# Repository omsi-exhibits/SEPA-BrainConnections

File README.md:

# OMSI's Brain Connections

## Next Steps
* update accelerometer code to use timers instead of delays
* update all the code to use timers instead of delays

## Other Todos
* consolodate notes
* write a good readme
* document High Level Design

## Known Bugs
none atm

# Flashing new firmware
The Itsybitsy32u4_5v is a litte finiky when it comes to flashing. The process that works most of the time for me is to double press the reset button
and then super quickly upload the code. Like within 300milliseconds or less. Maybe disabling serial.print()s would help? 

# Troubleshooting Tips
Removing and reinserting microcontroller is delicate and needs you to support the bottom of the mainboard with your hand.

## Fun Ideas
* Easter Egg Color pallette swap
* Sensor held on startup could change colors
* Handheld brain-connections game-thing

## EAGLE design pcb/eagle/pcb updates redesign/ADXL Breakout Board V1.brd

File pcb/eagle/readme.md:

sorry the file names are a mess. these were made before git versioning.
Use the highest numbered file names. If that is not it then its the newest written files.

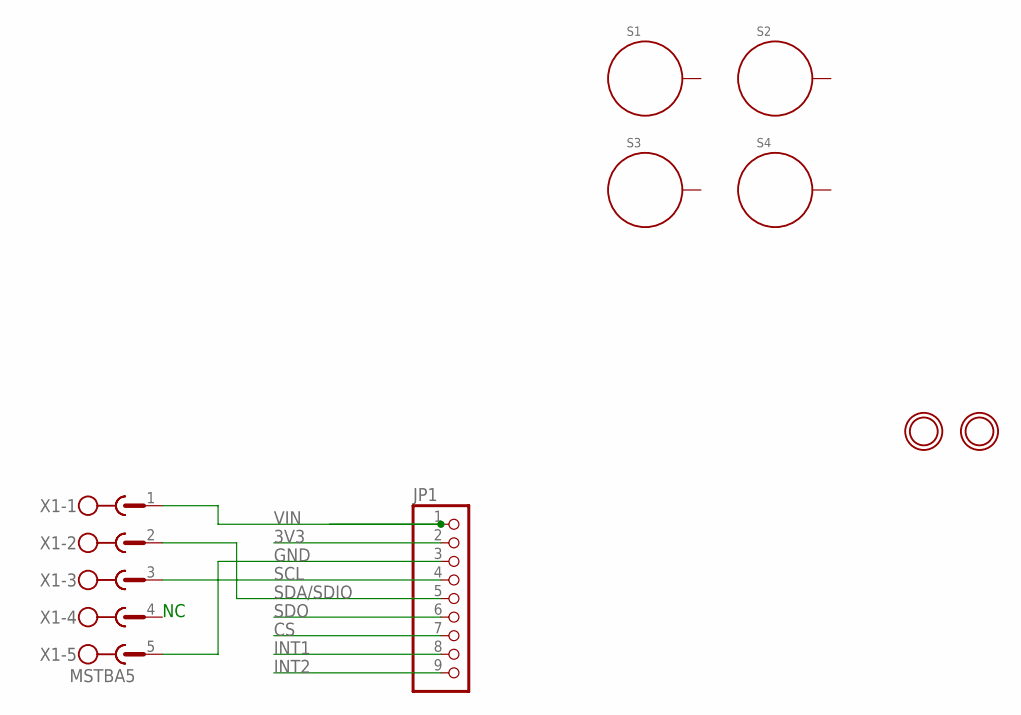
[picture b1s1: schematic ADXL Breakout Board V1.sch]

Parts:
JP1: HEADER-1X970MIL; 1X09_ROUND_70
S1, S2, S3, S4: STANDOFF_ELECTRICAL5-32; STANDOFF_ELECTRICAL_5_32
U$4, U$6: MOUNTINGHOLE2.5; MOUNTINGHOLE_2.5_PLATED
X1: MSTBA5

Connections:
3V3: JP1.2
CS: JP1.7
GND: JP1.3, X1.5
INT1: JP1.8
INT2: JP1.9
SCL: JP1.4, X1.3
SDA/SDIO: JP1.5, X1.2
SDO: JP1.6
VIN: JP1.1, X1.1

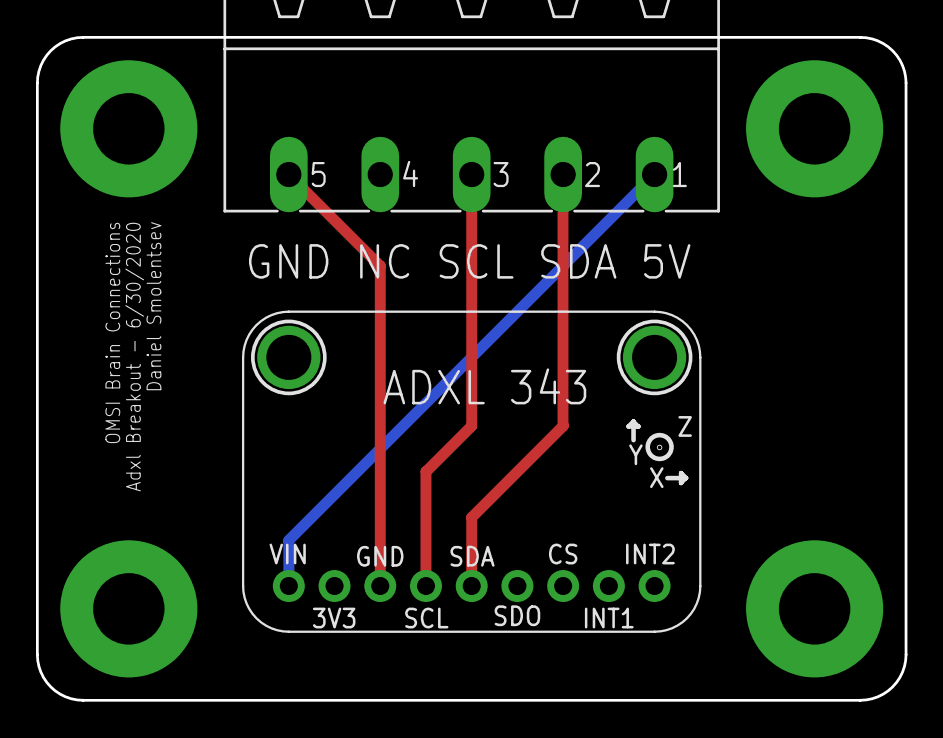
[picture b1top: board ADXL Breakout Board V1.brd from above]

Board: 2 copper layers, 48.3 x 36.8 mm, 8 parts (0 on the bottom side), 4 nets.

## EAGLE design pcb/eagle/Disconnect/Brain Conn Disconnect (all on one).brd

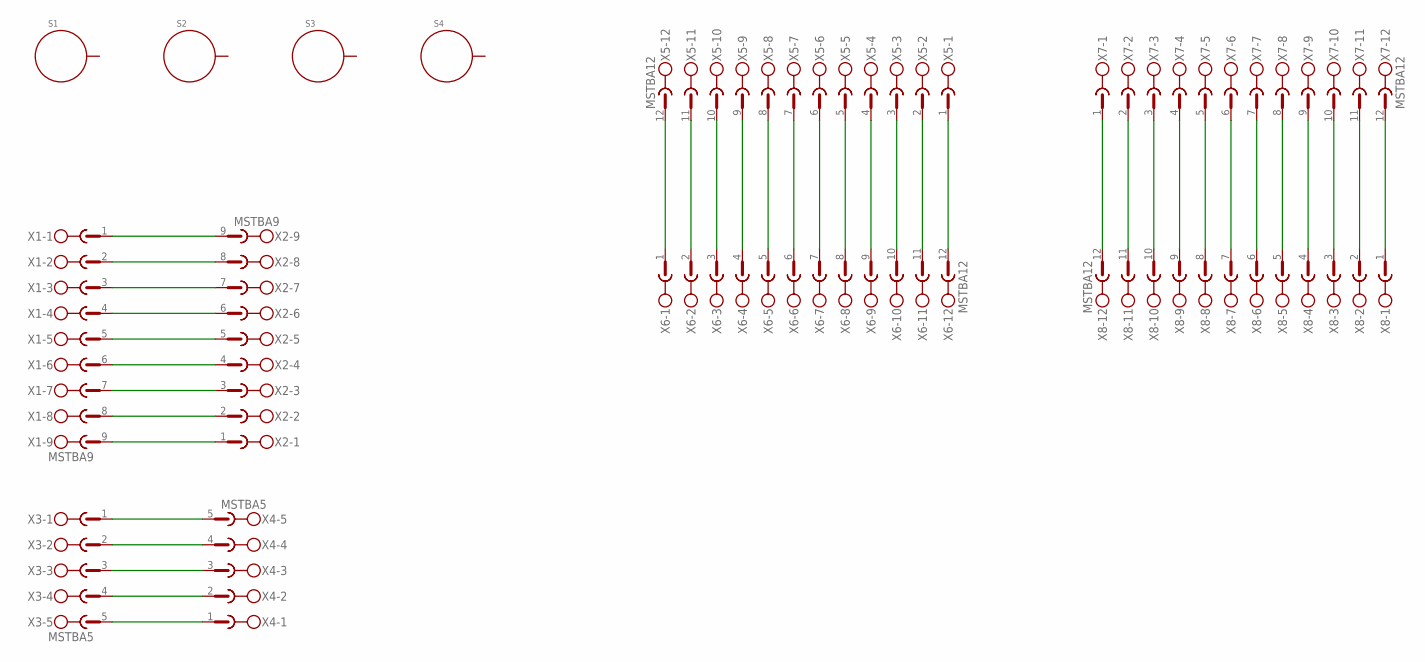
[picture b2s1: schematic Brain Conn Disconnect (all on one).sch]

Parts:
S1, S2, S3, S4: STANDOFF_ELECTRICAL144; STANDOFF_ELECTRICAL_144MILL_NORMAL_SCREW
X1, X2: MSTBA9
X3, X4: MSTBA5
X5, X6, X7, X8: MSTBA12

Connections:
unnamed: X3.1, X4.5
unnamed: X3.2, X4.4
unnamed: X3.3, X4.3
unnamed: X3.4, X4.2
unnamed: X3.5, X4.1
unnamed: X1.1, X2.9
unnamed: X1.2, X2.8
unnamed: X1.3, X2.7
unnamed: X1.4, X2.6
unnamed: X1.5, X2.5
unnamed: X1.6, X2.4
unnamed: X1.7, X2.3
unnamed: X1.8, X2.2
unnamed: X1.9, X2.1
unnamed: X5.12, X6.1
unnamed: X5.11, X6.2
unnamed: X5.10, X6.3
unnamed: X5.9, X6.4
unnamed: X5.8, X6.5
unnamed: X5.7, X6.6
unnamed: X5.6, X6.7
unnamed: X5.5, X6.8
unnamed: X5.4, X6.9
unnamed: X5.3, X6.10
unnamed: X5.2, X6.11
unnamed: X5.1, X6.12
unnamed: X7.1, X8.12
unnamed: X7.2, X8.11
unnamed: X7.3, X8.10
unnamed: X7.4, X8.9
unnamed: X7.5, X8.8
unnamed: X7.6, X8.7
unnamed: X7.7, X8.6
unnamed: X7.8, X8.5
unnamed: X7.9, X8.4
unnamed: X7.10, X8.3
unnamed: X7.11, X8.2
unnamed: X7.12, X8.1

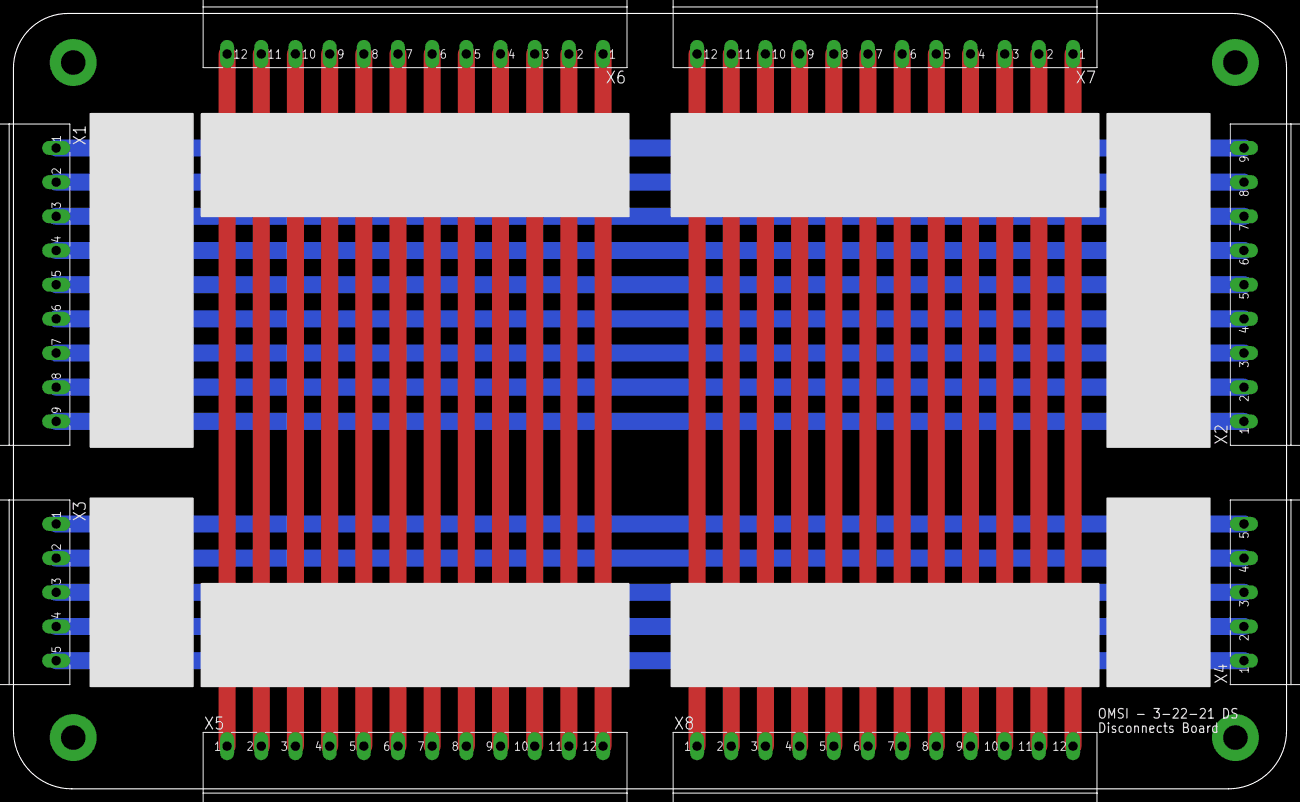
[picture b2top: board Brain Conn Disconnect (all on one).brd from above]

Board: 2 copper layers, 189.2 x 115.2 mm, 12 parts (0 on the bottom side), 38 nets.

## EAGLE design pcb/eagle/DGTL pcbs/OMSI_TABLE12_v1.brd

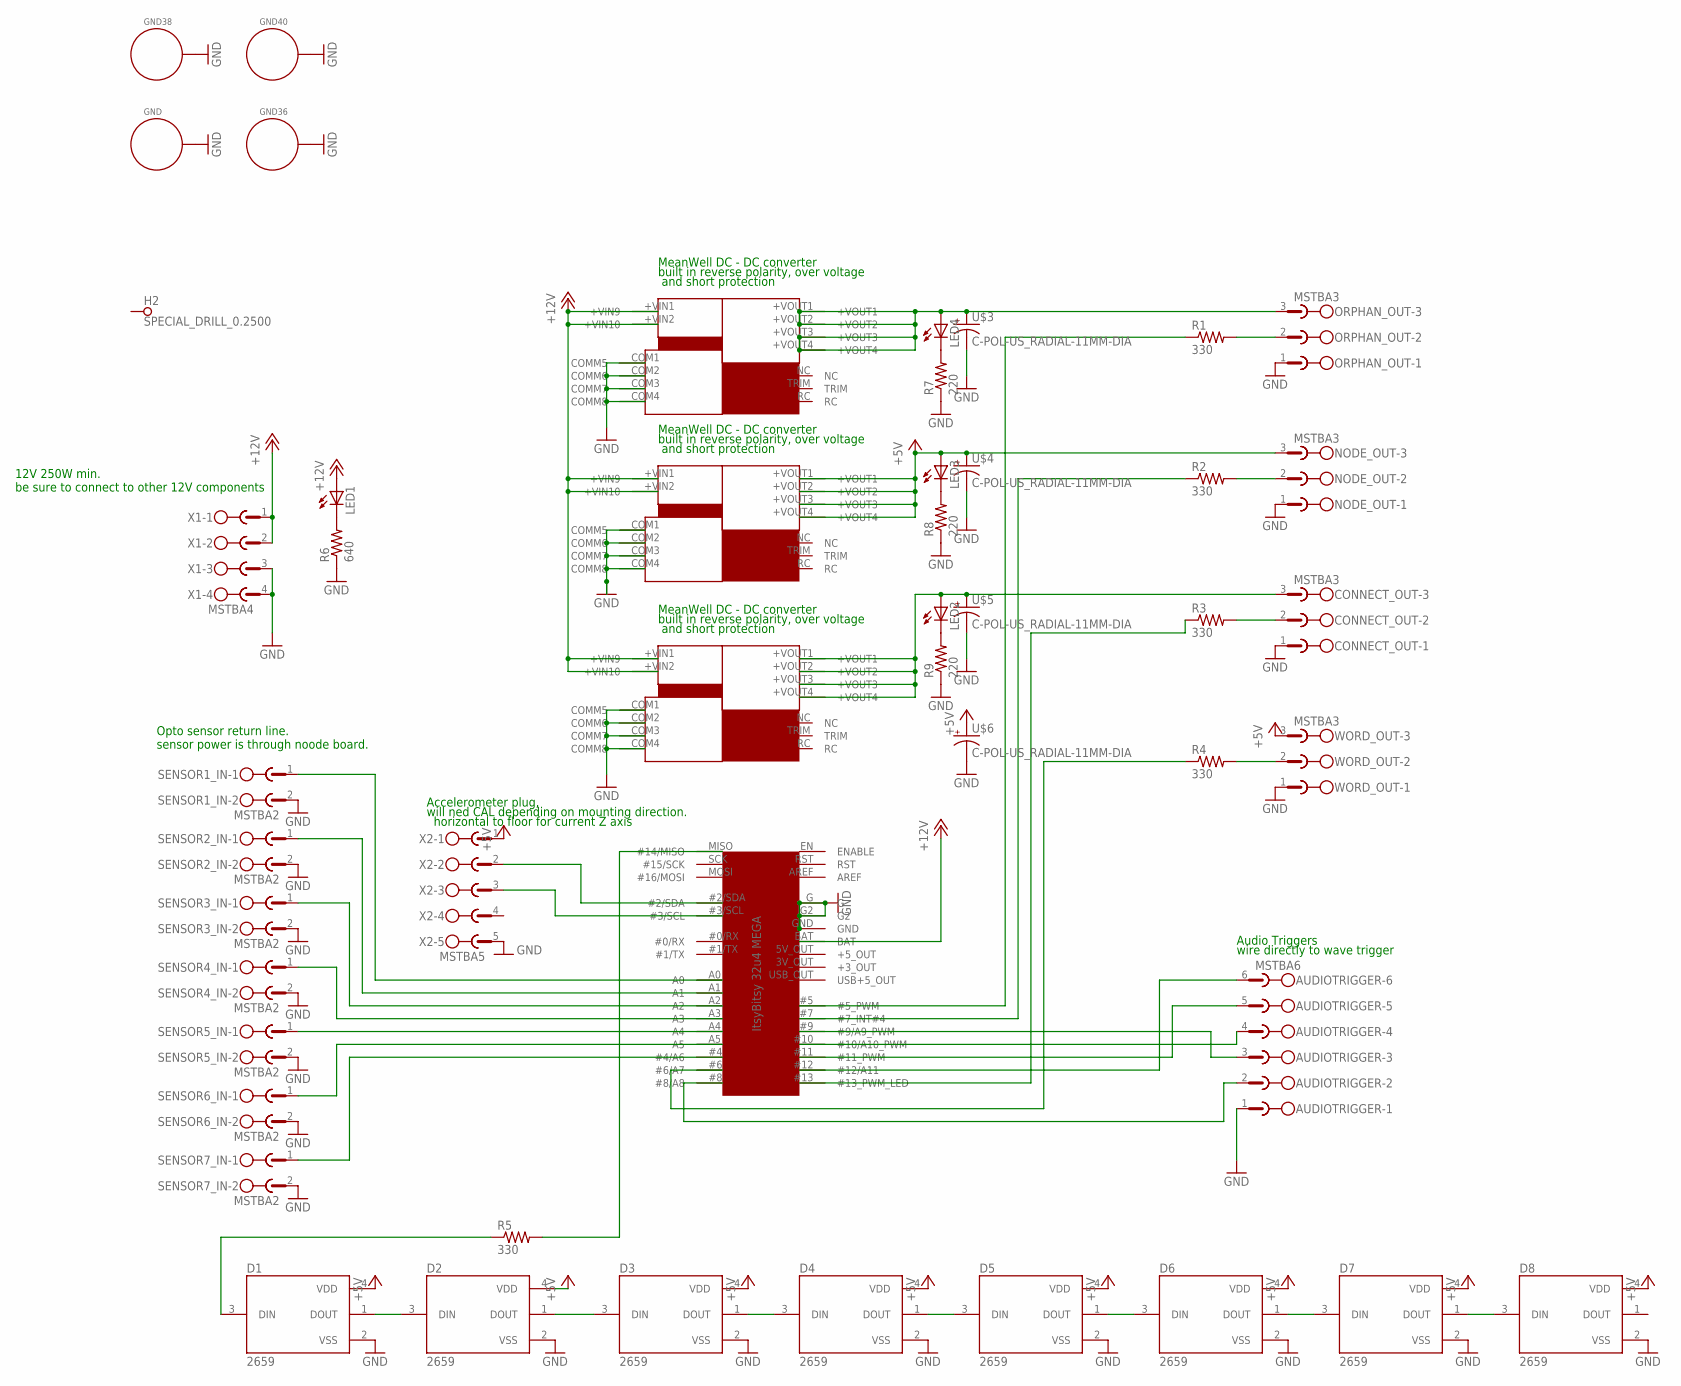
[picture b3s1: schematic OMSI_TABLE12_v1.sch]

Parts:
AUDIOTRIGGER: MSTBA6
CONNECT_OUT: MSTBA3
D1, D2, D3, D4, D5, D6, D7, D8: 2659
GND, GND36, GND38, GND40: STANDOFF_ELECTRICAL5-32; STANDOFF_ELECTRICAL_5_32
H2: SPECIAL_DRILL_0.2500; PAD_0.2500
LED1, LED2, LED3, LED4: LEDCHIPLED_1206; CHIPLED_1206
MEANWELL_NID100_1, MEANWELL_NID100_2, MEANWELL_NID100_3: MEANWELL_NID100
NODE_OUT: MSTBA3
ORPHAN_OUT: MSTBA3
R1, R2, R3, R4, R5: 330; RESAD1176W63L850D250B
R6: 640; R0805
R7, R8, R9: 220; R0805
SENSOR1_IN, SENSOR2_IN, SENSOR3_IN, SENSOR4_IN, SENSOR5_IN, SENSOR6_IN, SENSOR7_IN: MSTBA2
U$1: ITSYBITSY_32U4
U$3, U$4, U$5, U$6: C-POL-US_RADIAL-11MM-DIA; CAPPRD508W65D1000H1100B
WORD_OUT: MSTBA3
X1: MSTBA4
X2: MSTBA5

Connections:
+3_OUT: U$1.3V_OUT (+3_OUT)
+5V: D1.4 (VDD), D2.4 (VDD), D3.4 (VDD), D4.4 (VDD), D5.4 (VDD), D6.4 (VDD), D7.4 (VDD), D8.4 (VDD), LED3.A, MEANWELL_NID100_3.+VOUT1, MEANWELL_NID100_3.+VOUT2, MEANWELL_NID100_3.+VOUT3, MEANWELL_NID100_3.+VOUT4, NODE_OUT.3, U$4.1 (+), U$6.1 (+), WORD_OUT.3, X2.1
+5_OUT: U$1.5V_OUT (+5_OUT)
+12V: LED1.A, MEANWELL_NID100_1.+VIN1 (+VIN9), MEANWELL_NID100_1.+VIN2 (+VIN10), MEANWELL_NID100_2.+VIN1 (+VIN9), MEANWELL_NID100_2.+VIN2 (+VIN10), MEANWELL_NID100_3.+VIN1 (+VIN9), MEANWELL_NID100_3.+VIN2 (+VIN10), U$1.BAT, X1.1, X1.2
AREF: U$1.AREF
GND: AUDIOTRIGGER.1, CONNECT_OUT.1, D1.2 (VSS), D2.2 (VSS), D3.2 (VSS), D4.2 (VSS), D5.2 (VSS), D6.2 (VSS), D7.2 (VSS), D8.2 (VSS), GND.P1, GND36.P1, GND38.P1, GND40.P1, MEANWELL_NID100_1.COM1 (COMM5), MEANWELL_NID100_1.COM2 (COMM6), MEANWELL_NID100_1.COM3 (COMM7), MEANWELL_NID100_1.COM4 (COMM8), MEANWELL_NID100_2.COM1 (COMM5), MEANWELL_NID100_2.COM2 (COMM6), MEANWELL_NID100_2.COM3 (COMM7), MEANWELL_NID100_2.COM4 (COMM8), MEANWELL_NID100_3.COM1 (COMM5), MEANWELL_NID100_3.COM2 (COMM6), MEANWELL_NID100_3.COM3 (COMM7), MEANWELL_NID100_3.COM4 (COMM8), NODE_OUT.1, ORPHAN_OUT.1, R6.1, R7.1, R8.1, R9.1, SENSOR1_IN.2, SENSOR2_IN.2, SENSOR3_IN.2, SENSOR4_IN.2, SENSOR5_IN.2, SENSOR6_IN.2, SENSOR7_IN.2, U$1.G, U$1.G2, U$1.GND, U$3.2 (-), U$4.2 (-), U$5.2 (-), U$6.2 (-), WORD_OUT.1, X1.3, X1.4, X2.5
unnamed: LED4.A, MEANWELL_NID100_2.+VOUT1, MEANWELL_NID100_2.+VOUT2, MEANWELL_NID100_2.+VOUT3, MEANWELL_NID100_2.+VOUT4, ORPHAN_OUT.3, U$3.1 (+)
unnamed: U$1.#2/SDA, X2.2
unnamed: U$1.#3/SCL, X2.3
unnamed: SENSOR1_IN.1, U$1.A0
unnamed: SENSOR2_IN.1, U$1.A1
unnamed: SENSOR3_IN.1, U$1.A2
unnamed: CONNECT_OUT.3, LED2.A, MEANWELL_NID100_1.+VOUT1, MEANWELL_NID100_1.+VOUT2, MEANWELL_NID100_1.+VOUT3, MEANWELL_NID100_1.+VOUT4, U$5.1 (+)
unnamed: SENSOR4_IN.1, U$1.A3
unnamed: ORPHAN_OUT.2, R1.2
unnamed: R1.1, U$1.#5 (#5_PWM)
unnamed: NODE_OUT.2, R2.2
unnamed: SENSOR5_IN.1, U$1.A4
unnamed: SENSOR6_IN.1, U$1.A5
unnamed: SENSOR7_IN.1, U$1.#4 (#4/A6)
unnamed: R2.1, U$1.#7 (#7_INT#4)
unnamed: CONNECT_OUT.2, R3.2
unnamed: R3.1, U$1.#13 (#13_PWM_LED)
unnamed: R4.2, WORD_OUT.2
unnamed: R4.1, U$1.#6 (#6/A7)
unnamed: AUDIOTRIGGER.6, U$1.#12 (#12/A11)
unnamed: AUDIOTRIGGER.5, U$1.#11 (#11_PWM)
unnamed: R5.2, U$1.MISO (#14/MISO)
unnamed: AUDIOTRIGGER.4, U$1.#10 (#10/A10_PWM)
unnamed: AUDIOTRIGGER.3, U$1.#9 (#9/A9_PWM)
unnamed: AUDIOTRIGGER.2, U$1.#8 (#8/A8)
unnamed: D1.1 (DOUT), D2.3 (DIN)
unnamed: D2.1 (DOUT), D3.3 (DIN)
unnamed: D3.1 (DOUT), D4.3 (DIN)
unnamed: D4.1 (DOUT), D5.3 (DIN)
unnamed: D5.1 (DOUT), D6.3 (DIN)
unnamed: D6.1 (DOUT), D7.3 (DIN)
unnamed: D7.1 (DOUT), D8.3 (DIN)
unnamed: D1.3 (DIN), R5.1
unnamed: LED1.C, R6.2
unnamed: LED4.C, R7.2
unnamed: LED3.C, R8.2
unnamed: LED2.C, R9.2
RST: U$1.RST
USB+5_OUT: U$1.USB_OUT (USB+5_OUT)

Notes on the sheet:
12V 250W min. be sure to connect to other 12V components
Opto sensor return line. sensor power is through noode board.
Accelerometer plug, will ned CAL depending on mounting direction. horizontal to floor for current Z axis
MeanWell DC - DC converter built in reverse polarity, over voltage and short protection
Audio Triggers wire directly to wave trigger

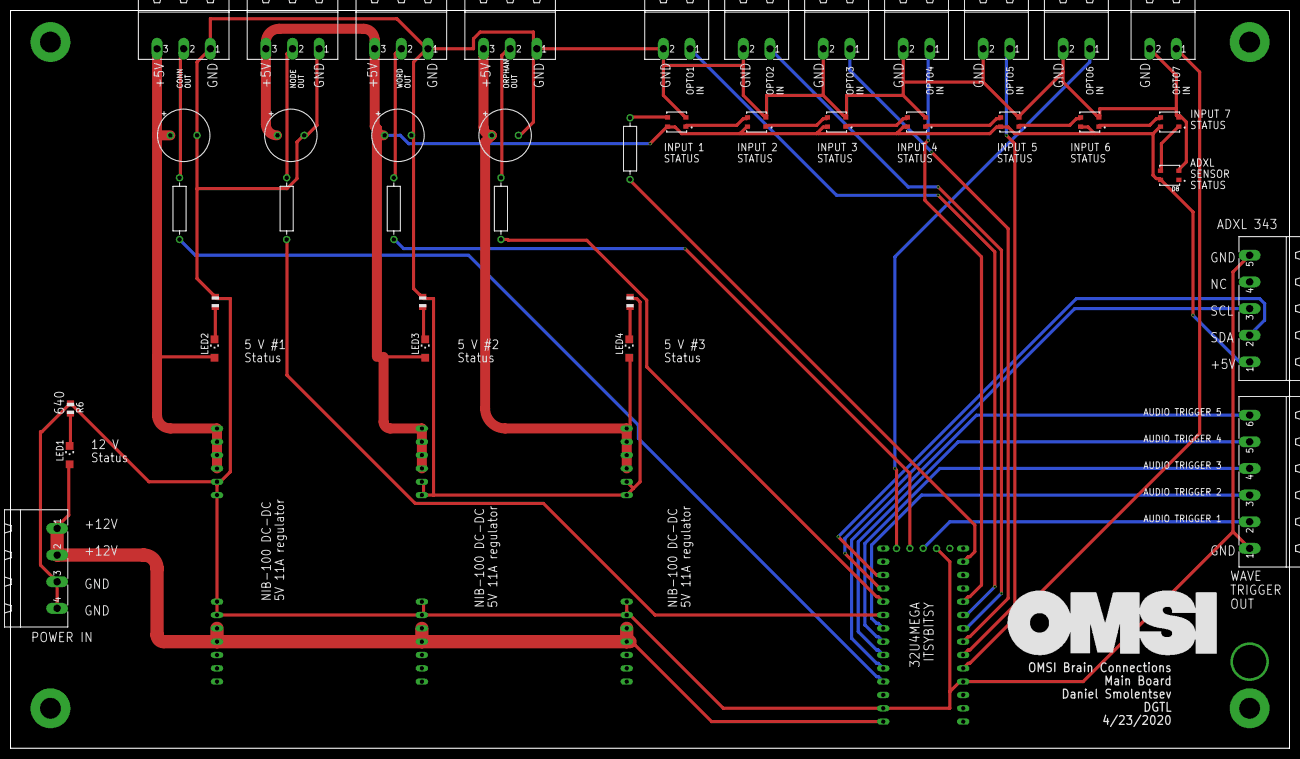
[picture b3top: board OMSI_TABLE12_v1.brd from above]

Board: 2 copper layers, 243.8 x 140.6 mm, 48 parts (0 on the bottom side), 40 nets.

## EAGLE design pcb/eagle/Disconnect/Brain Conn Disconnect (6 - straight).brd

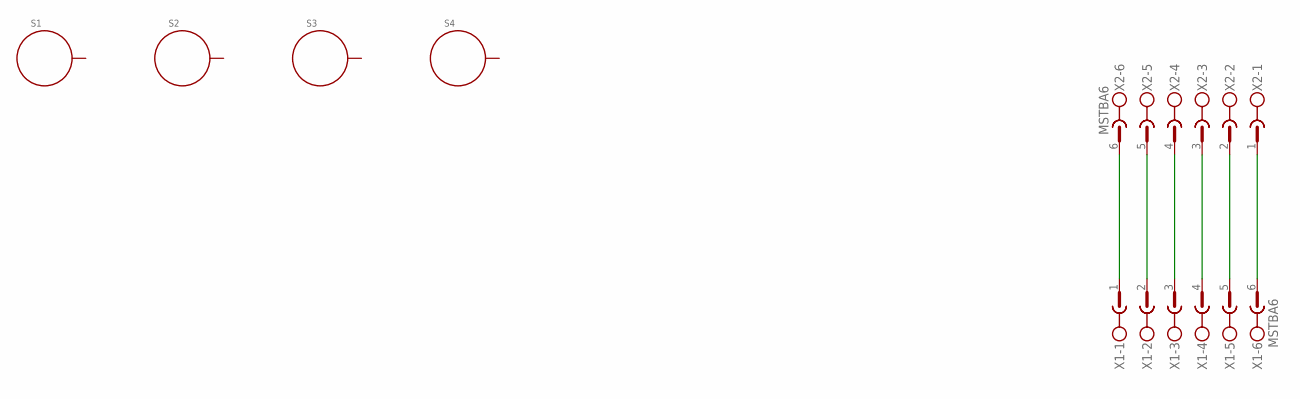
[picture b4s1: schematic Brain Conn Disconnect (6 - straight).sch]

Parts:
S1, S2, S3, S4: STANDOFF_ELECTRICAL144; STANDOFF_ELECTRICAL_144MILL_NORMAL_SCREW
X1, X2: MSTBA6

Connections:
unnamed: X1.1, X2.6
unnamed: X1.2, X2.5
unnamed: X1.3, X2.4
unnamed: X1.4, X2.3
unnamed: X1.5, X2.2
unnamed: X1.6, X2.1

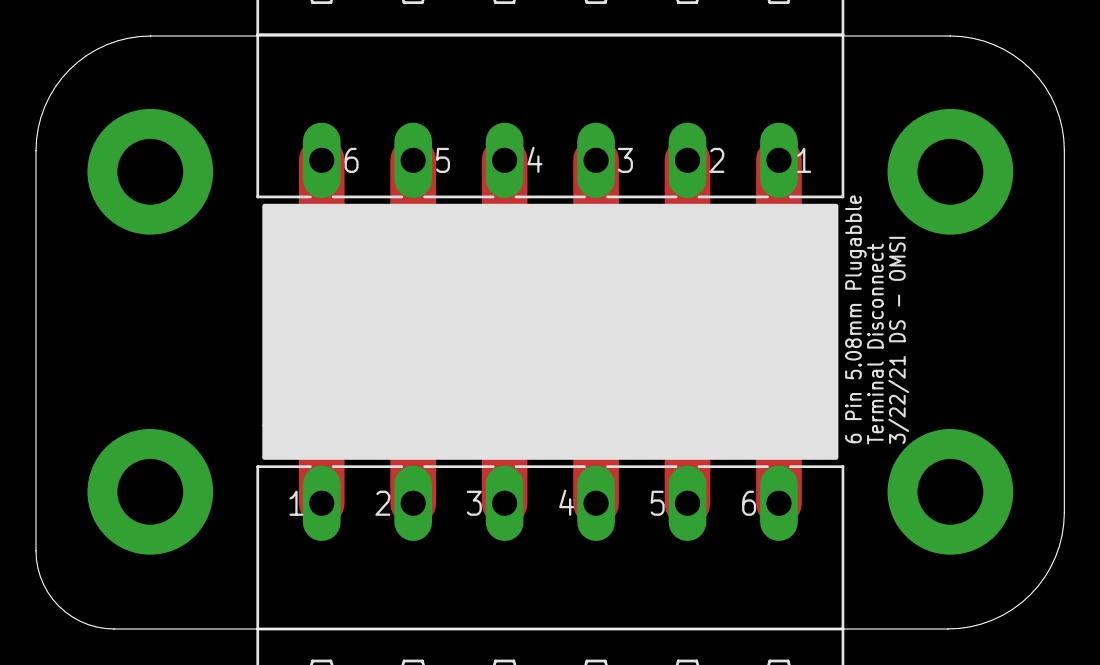
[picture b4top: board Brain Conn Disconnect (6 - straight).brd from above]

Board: 2 copper layers, 57.1 x 32.9 mm, 6 parts (0 on the bottom side), 6 nets.

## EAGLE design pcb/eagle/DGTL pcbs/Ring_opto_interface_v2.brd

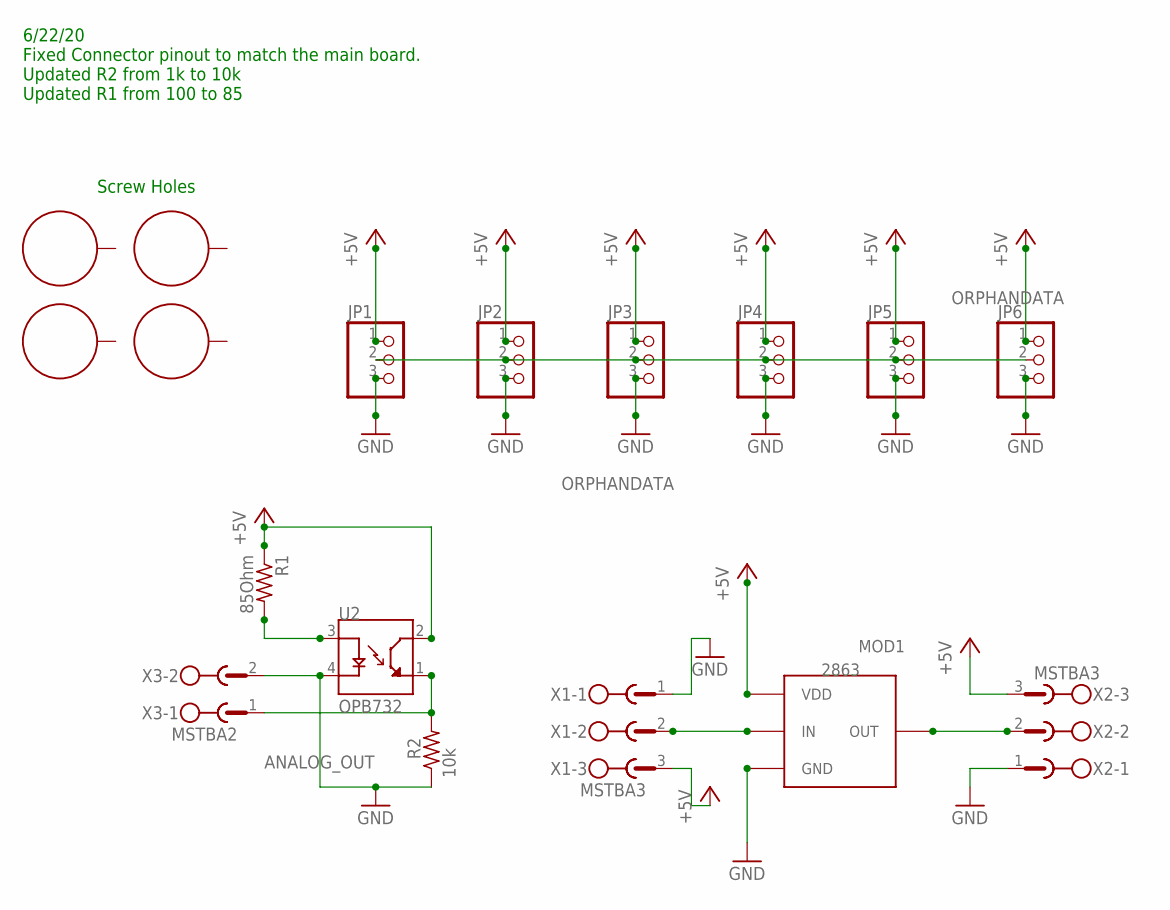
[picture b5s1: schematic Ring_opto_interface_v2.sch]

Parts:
H1, H2, H3, H4: STANDOFF_ELECTRICAL5-32; STANDOFF_ELECTRICAL_5_32
JP1, JP2, JP3, JP4, JP5, JP6: PINHD-1X3CB; 1X03-CLEANBIG
MOD1: 2863; ADAFRUIT_2863
R1: 85Ohm; RESAD1176W63L850D250B
R2: 10k; RESAD1176W63L850D250B
U2: OPB732; OPTO_OPB732
X1, X2: MSTBA3
X3: MSTBA2

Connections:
+5V: JP1.1, JP2.1, JP3.1, JP4.1, JP5.1, JP6.1, MOD1.VDD1 (VDD), MOD1.VDD2 (VDD), R1.1, U2.2 (CT), X1.3, X2.3
ANALOG_OUT: R2.2, U2.1 (ET), X3.1
GND: JP1.3, JP2.3, JP3.3, JP4.3, JP5.3, JP6.3, MOD1.GND1 (GND), MOD1.GND2 (GND), R2.1, U2.4 (C), X1.1, X2.1, X3.2
unnamed: R1.2, U2.3 (A)
unnamed: MOD1.IN, X1.2
unnamed: MOD1.OUT, X2.2
ORPHANDATA: JP1.2, JP2.2, JP3.2, JP4.2, JP5.2, JP6.2

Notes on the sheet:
Screw Holes
6/22/20 Fixed Connector pinout to match the main board. Updated R2 from 1k to 10k Updated R1 from 100 to 85

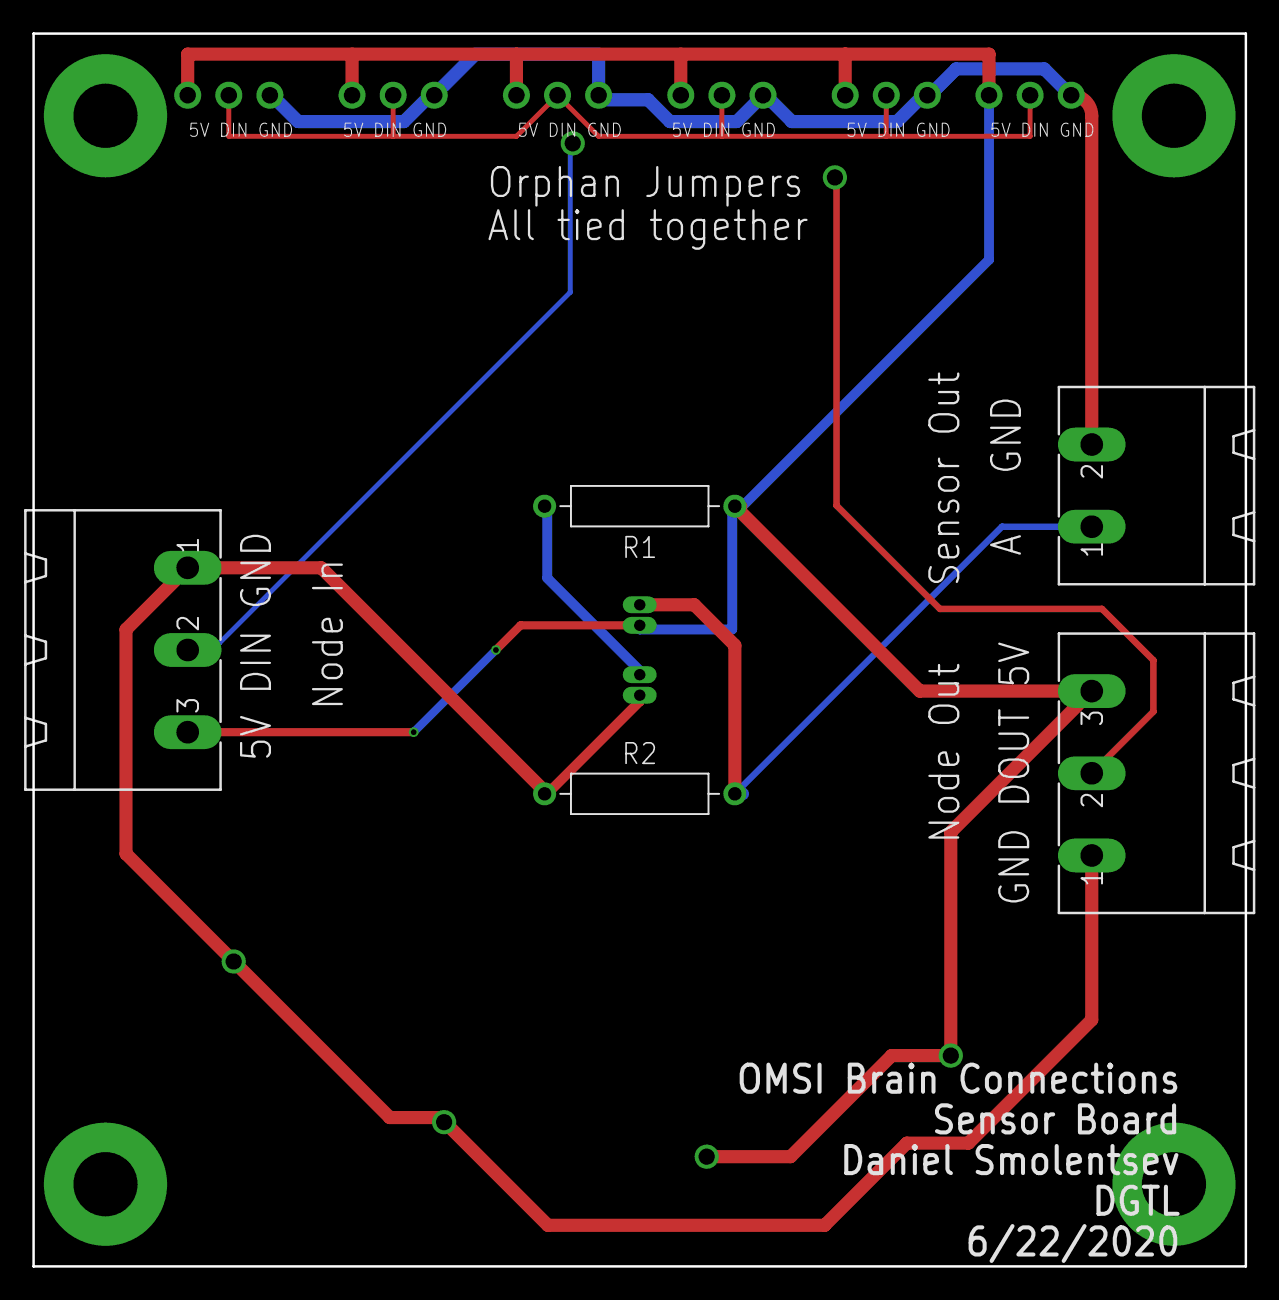
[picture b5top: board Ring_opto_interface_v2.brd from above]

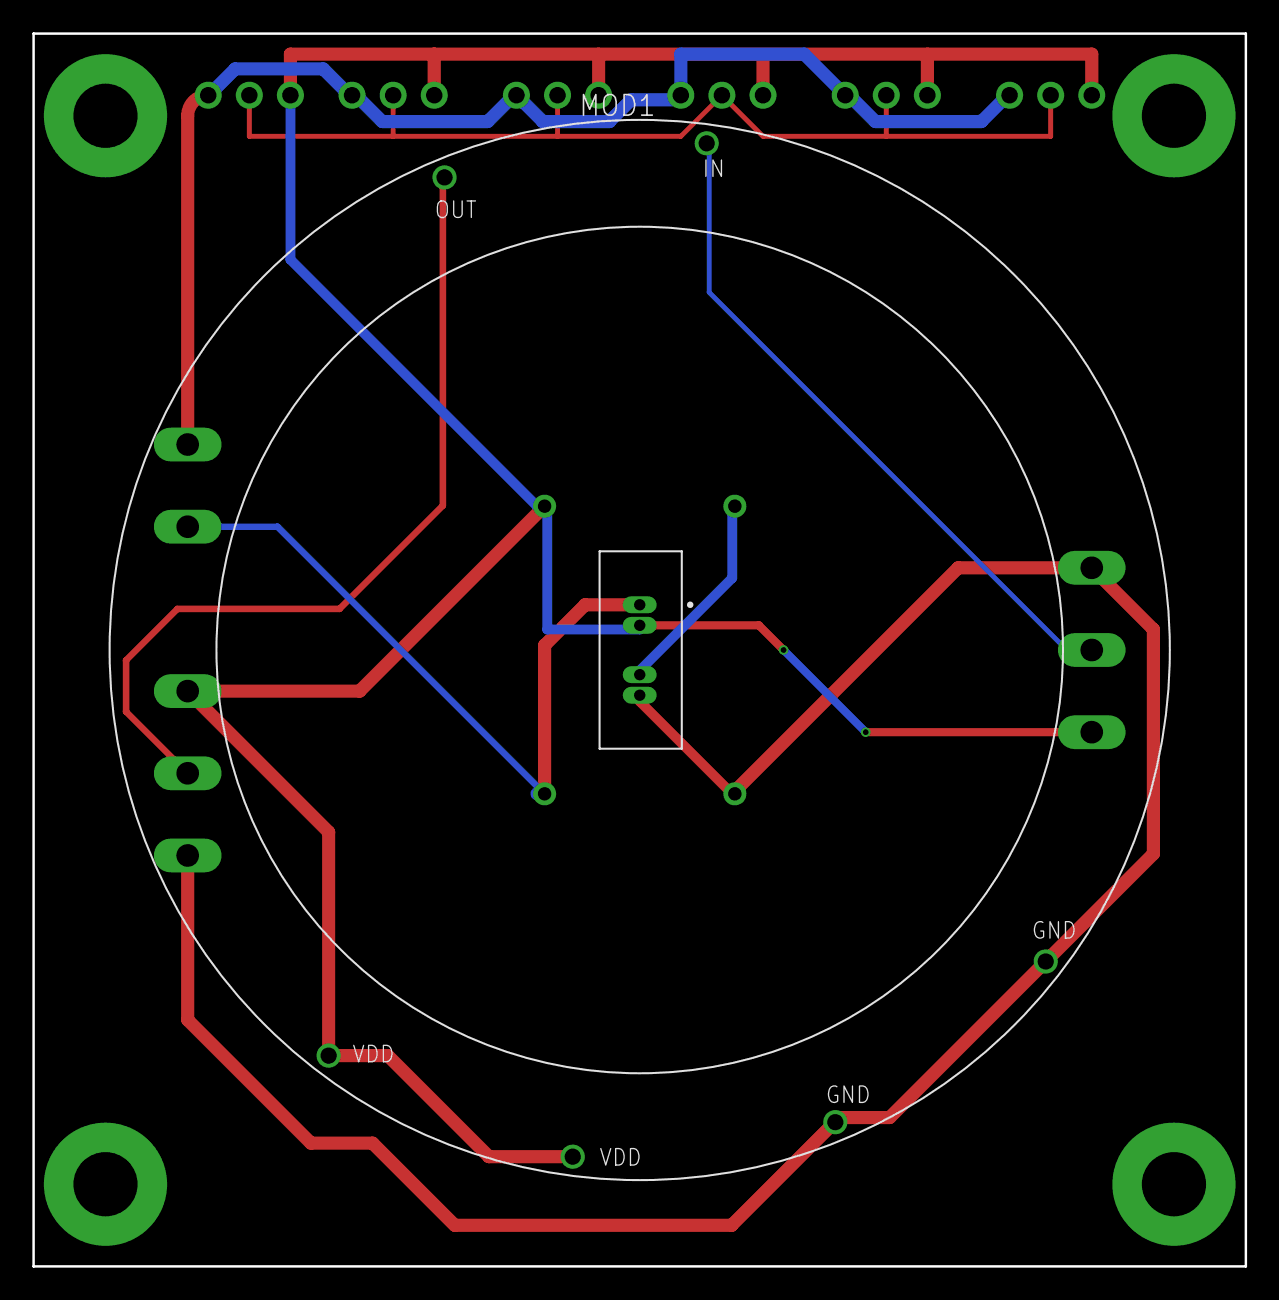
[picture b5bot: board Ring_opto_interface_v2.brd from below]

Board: 2 copper layers, 74.9 x 76.2 mm, 17 parts (2 on the bottom side), 7 nets.

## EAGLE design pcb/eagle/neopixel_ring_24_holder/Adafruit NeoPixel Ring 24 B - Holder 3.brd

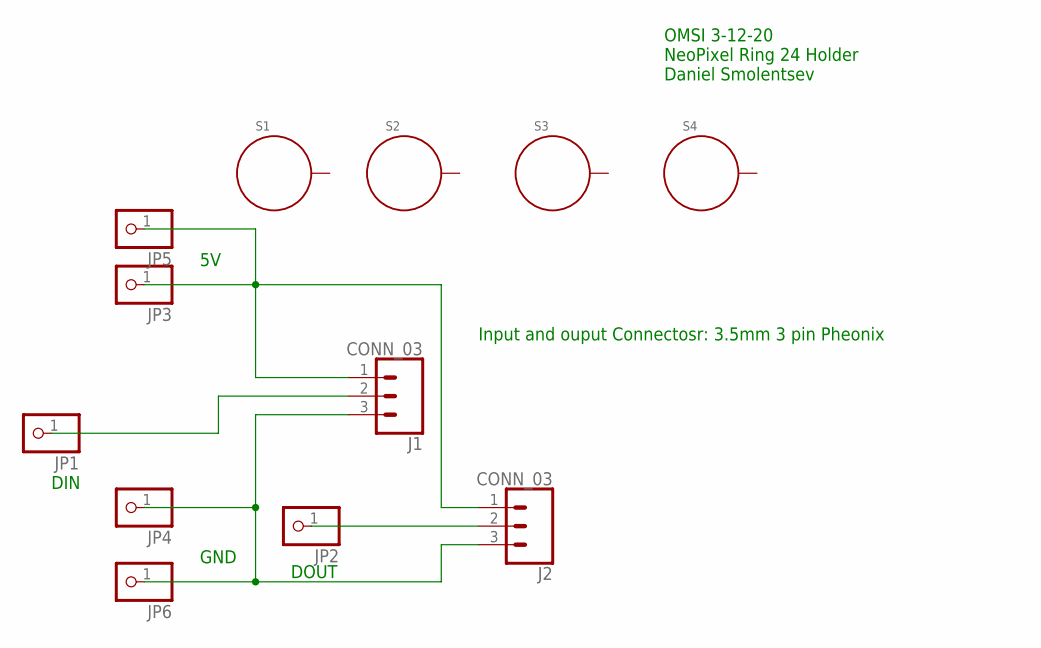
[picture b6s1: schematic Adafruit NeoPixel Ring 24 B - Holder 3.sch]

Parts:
J1, J2: CONN_03; 1X03_3.5MM_RA
JP1, JP2, JP3, JP4, JP5, JP6: PINHD-1X1CB; 1X01-CLEANBIG
S1, S2, S3, S4: STANDOFF_ELECTRICAL.17"; STANDOFF-ELECTRICAL

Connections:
unnamed: J1.1, J2.1, JP3.1, JP5.1
unnamed: J1.3, J2.3, JP4.1, JP6.1
unnamed: J1.2, JP1.1
unnamed: J2.2, JP2.1

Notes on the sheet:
GND
DIN
DOUT
Input and ouput Connectosr: 3.5mm 3 pin Pheonix
OMSI 3-12-20 NeoPixel Ring 24 Holder Daniel Smolentsev

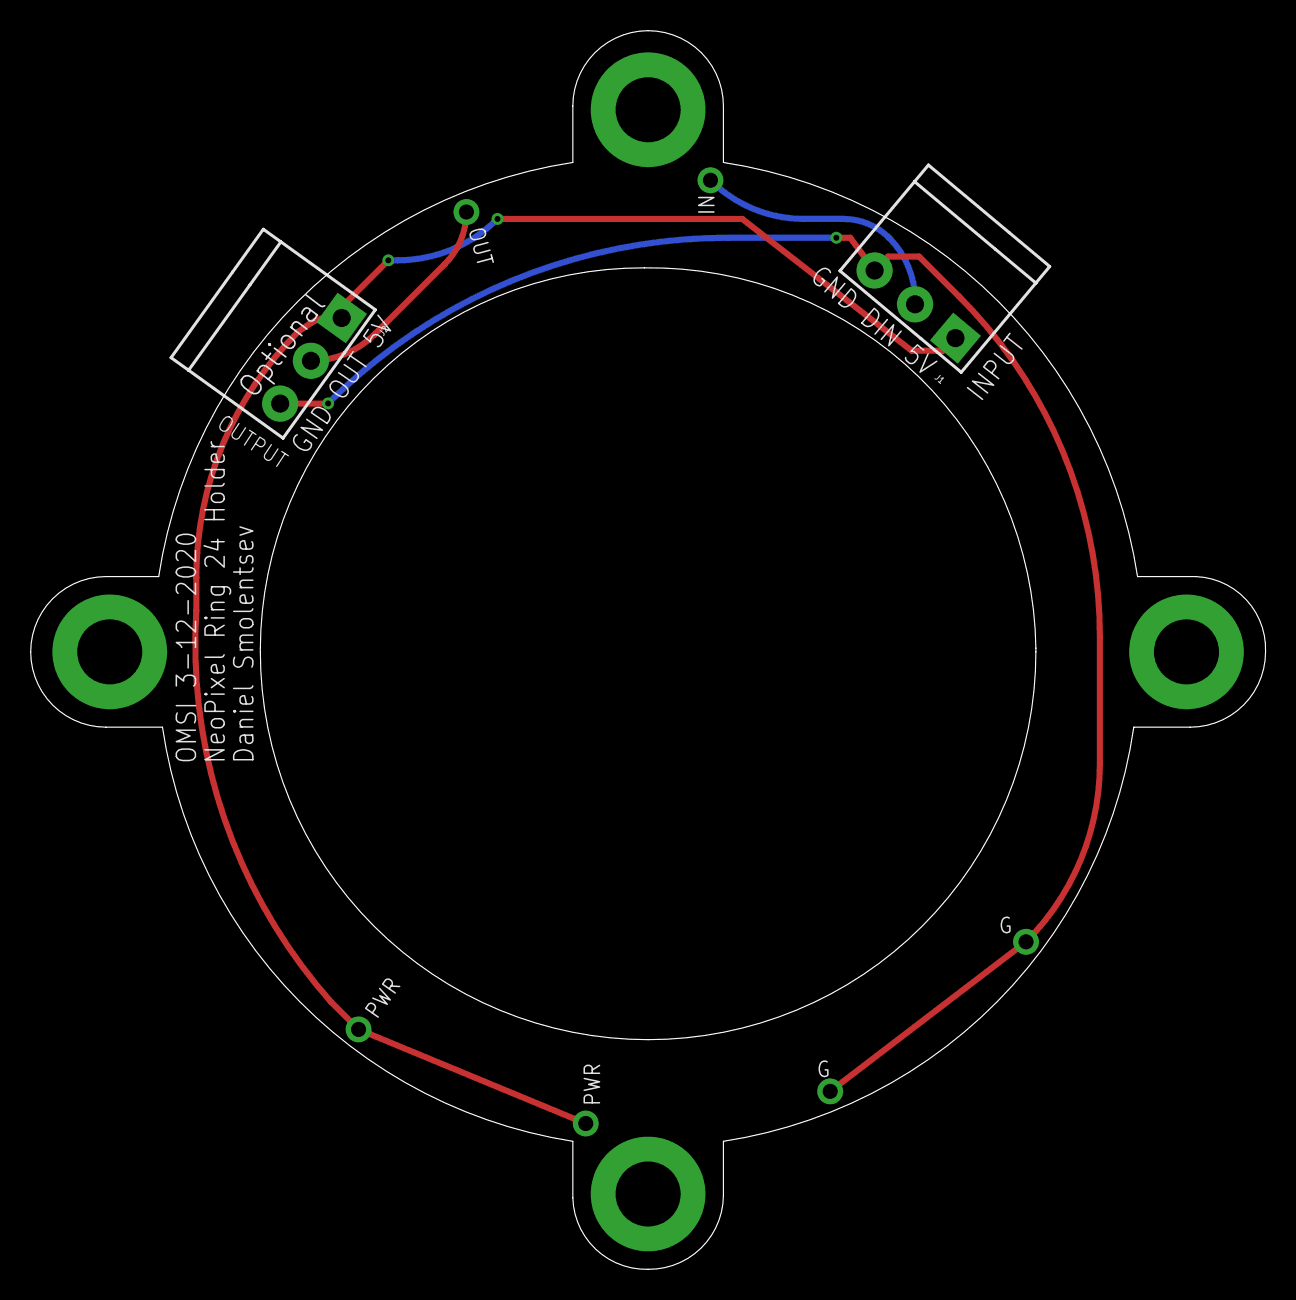
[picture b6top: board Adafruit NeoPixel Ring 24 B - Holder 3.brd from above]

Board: 2 copper layers, 82.0 x 82.2 mm, 12 parts (0 on the bottom side), 4 nets.

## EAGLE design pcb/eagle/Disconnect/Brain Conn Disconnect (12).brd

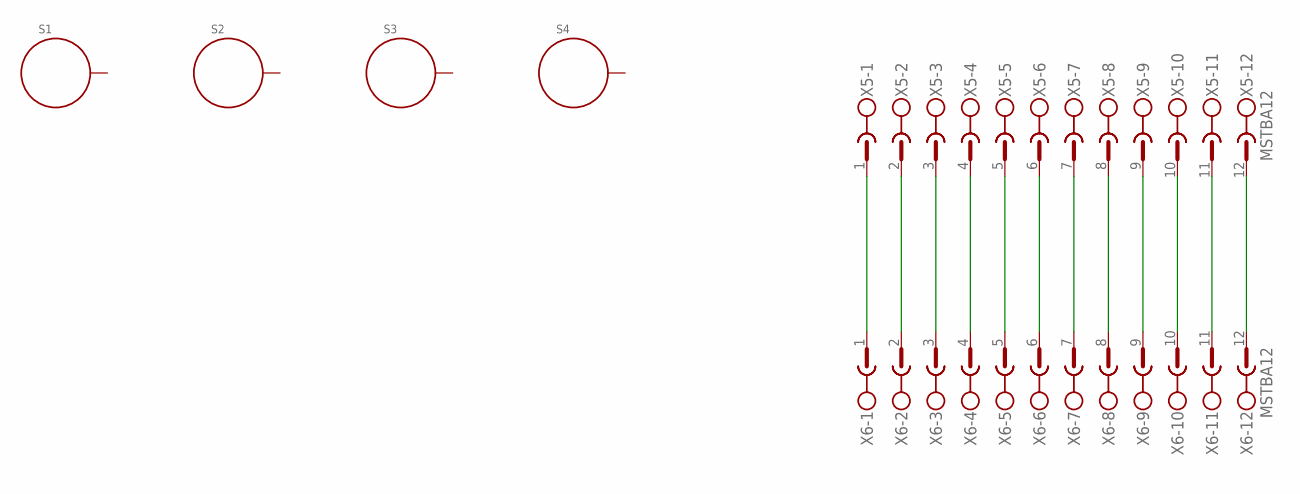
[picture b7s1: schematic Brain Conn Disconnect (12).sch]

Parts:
S1, S2, S3, S4: STANDOFF_ELECTRICAL144; STANDOFF_ELECTRICAL_144MILL_NORMAL_SCREW
X5, X6: MSTBA12

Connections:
unnamed: X5.1, X6.1
unnamed: X5.2, X6.2
unnamed: X5.3, X6.3
unnamed: X5.4, X6.4
unnamed: X5.5, X6.5
unnamed: X5.6, X6.6
unnamed: X5.7, X6.7
unnamed: X5.8, X6.8
unnamed: X5.9, X6.9
unnamed: X5.10, X6.10
unnamed: X5.11, X6.11
unnamed: X5.12, X6.12

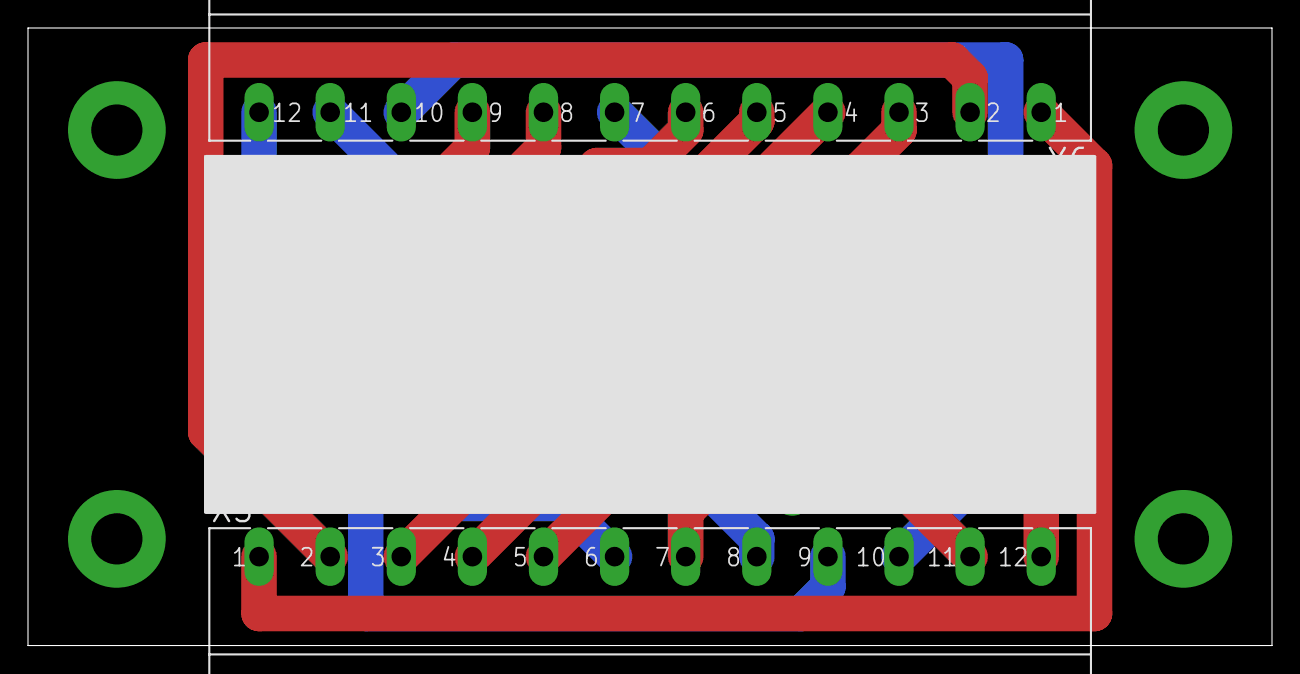
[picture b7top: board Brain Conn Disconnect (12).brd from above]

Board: 2 copper layers, 88.9 x 44.1 mm, 6 parts (0 on the bottom side), 12 nets.

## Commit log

2021-06-16 init commit
2021-06-16 Started readme

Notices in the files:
parts and their libraries:
microbuilder: This work is placed in the public domain, and may be freely used for commercial and non-commercial work with the following conditions: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
